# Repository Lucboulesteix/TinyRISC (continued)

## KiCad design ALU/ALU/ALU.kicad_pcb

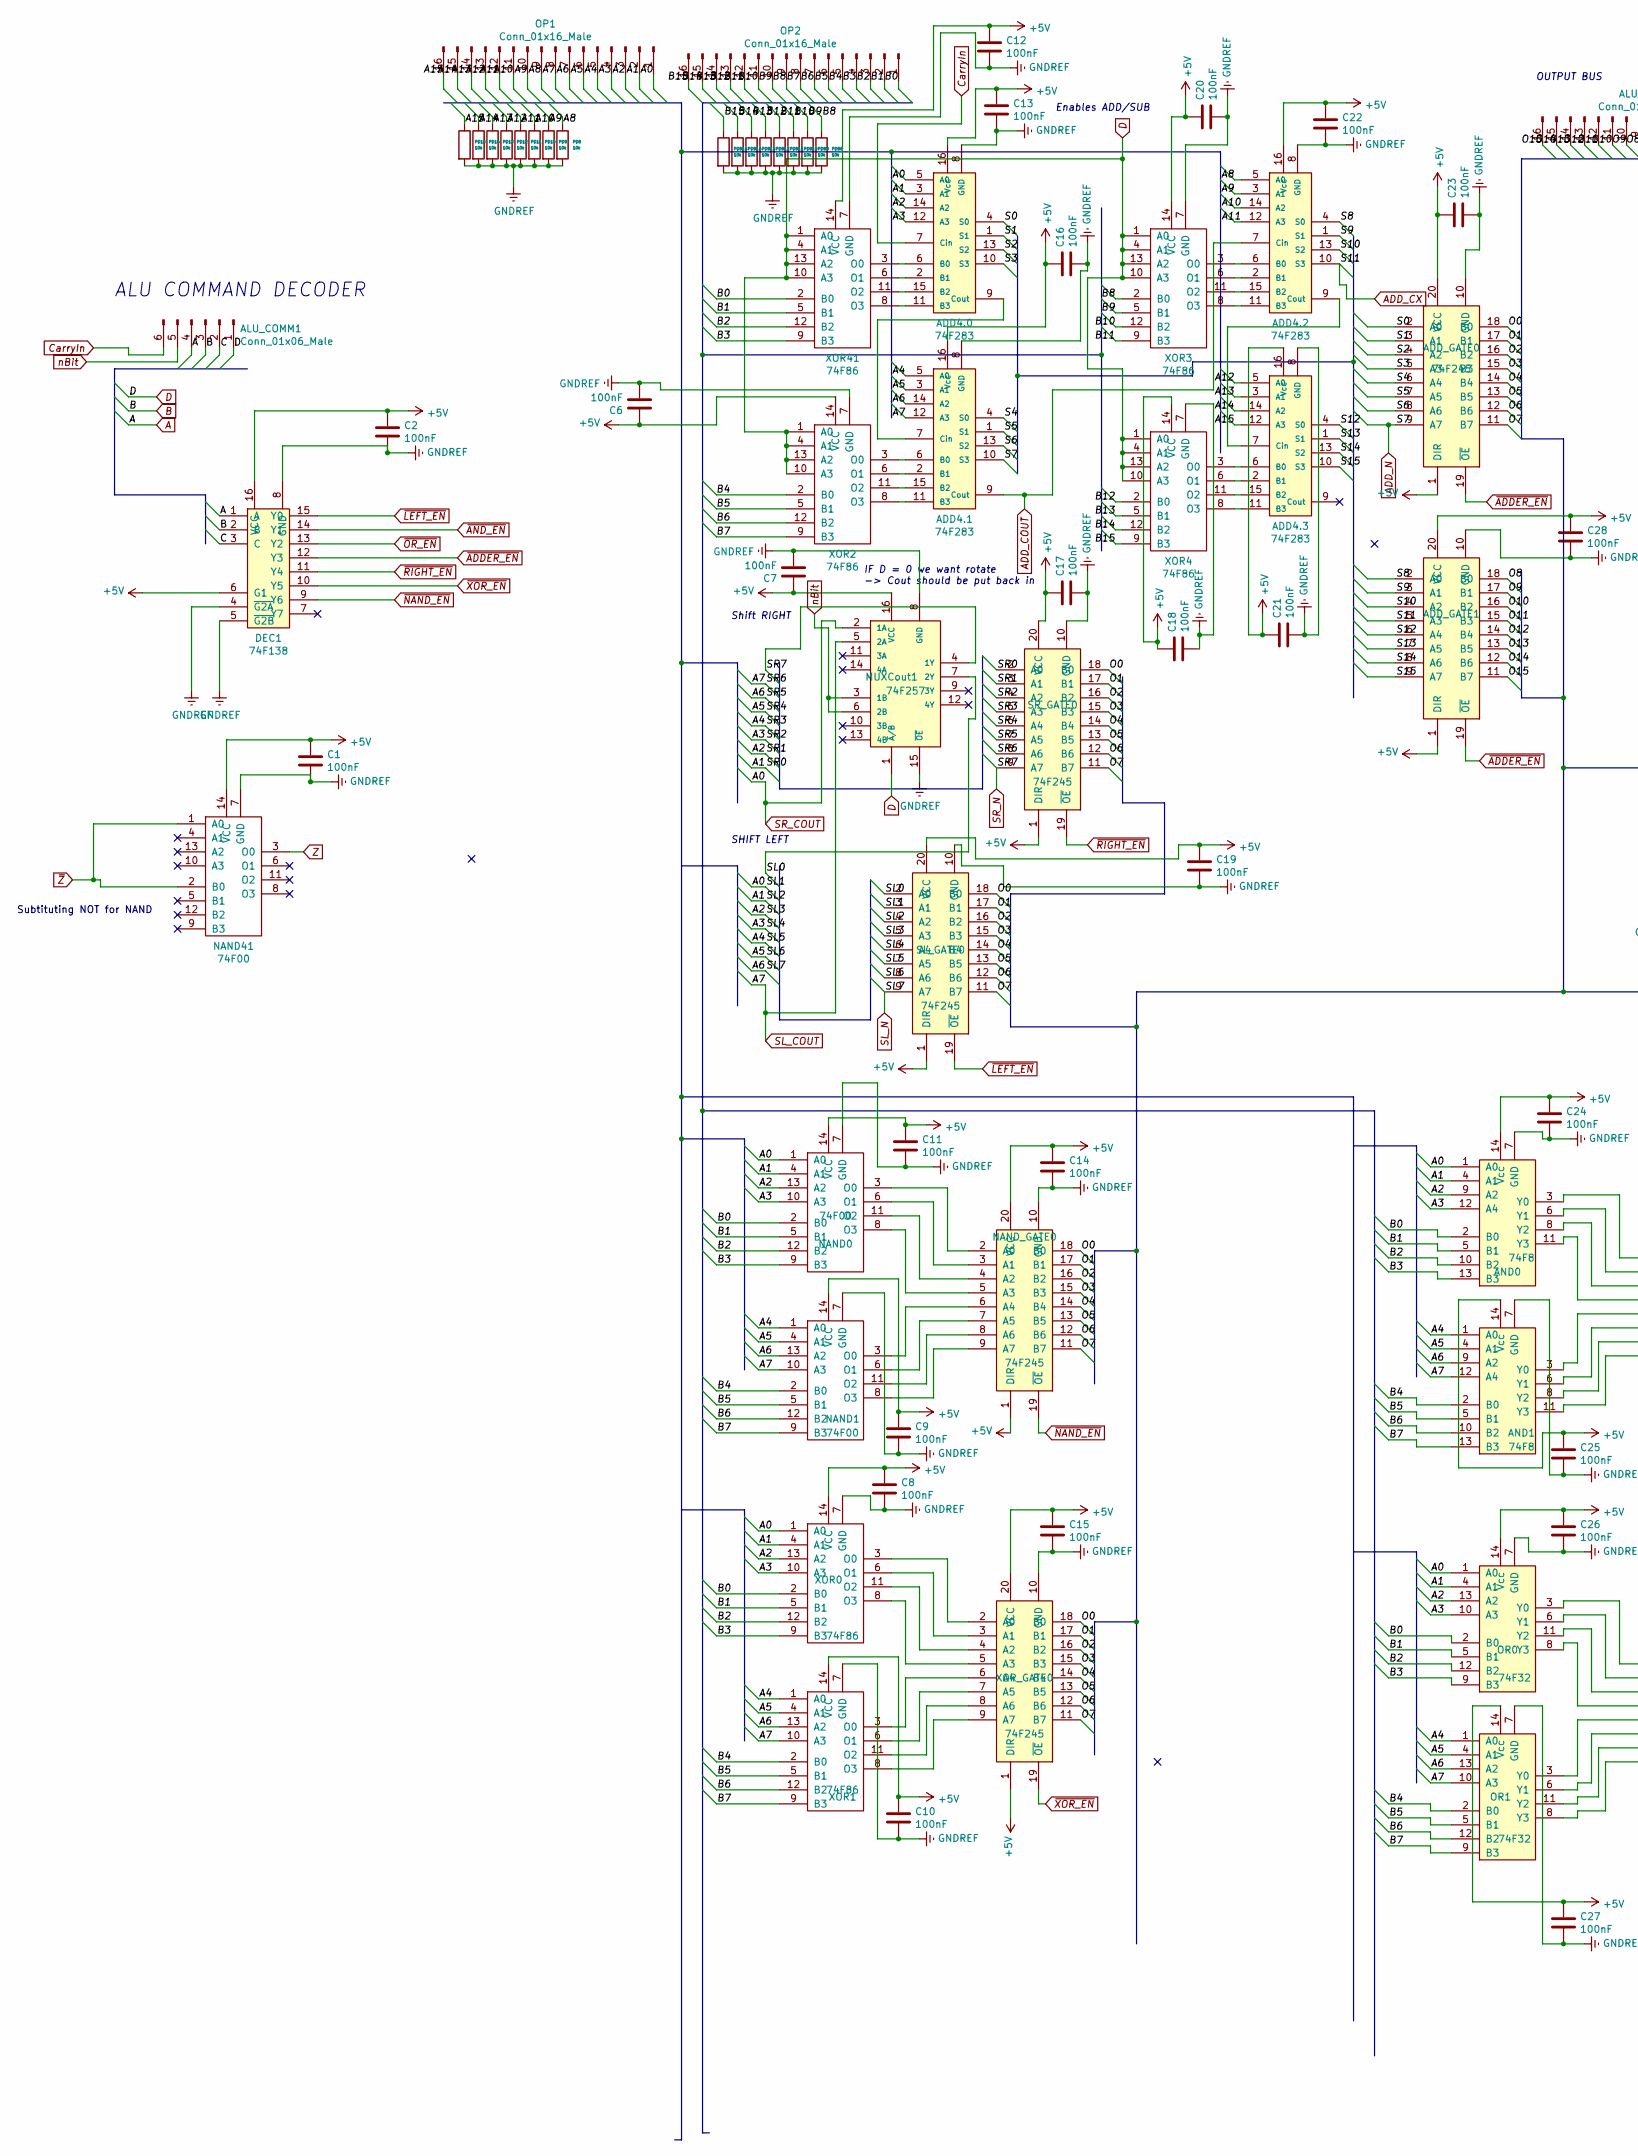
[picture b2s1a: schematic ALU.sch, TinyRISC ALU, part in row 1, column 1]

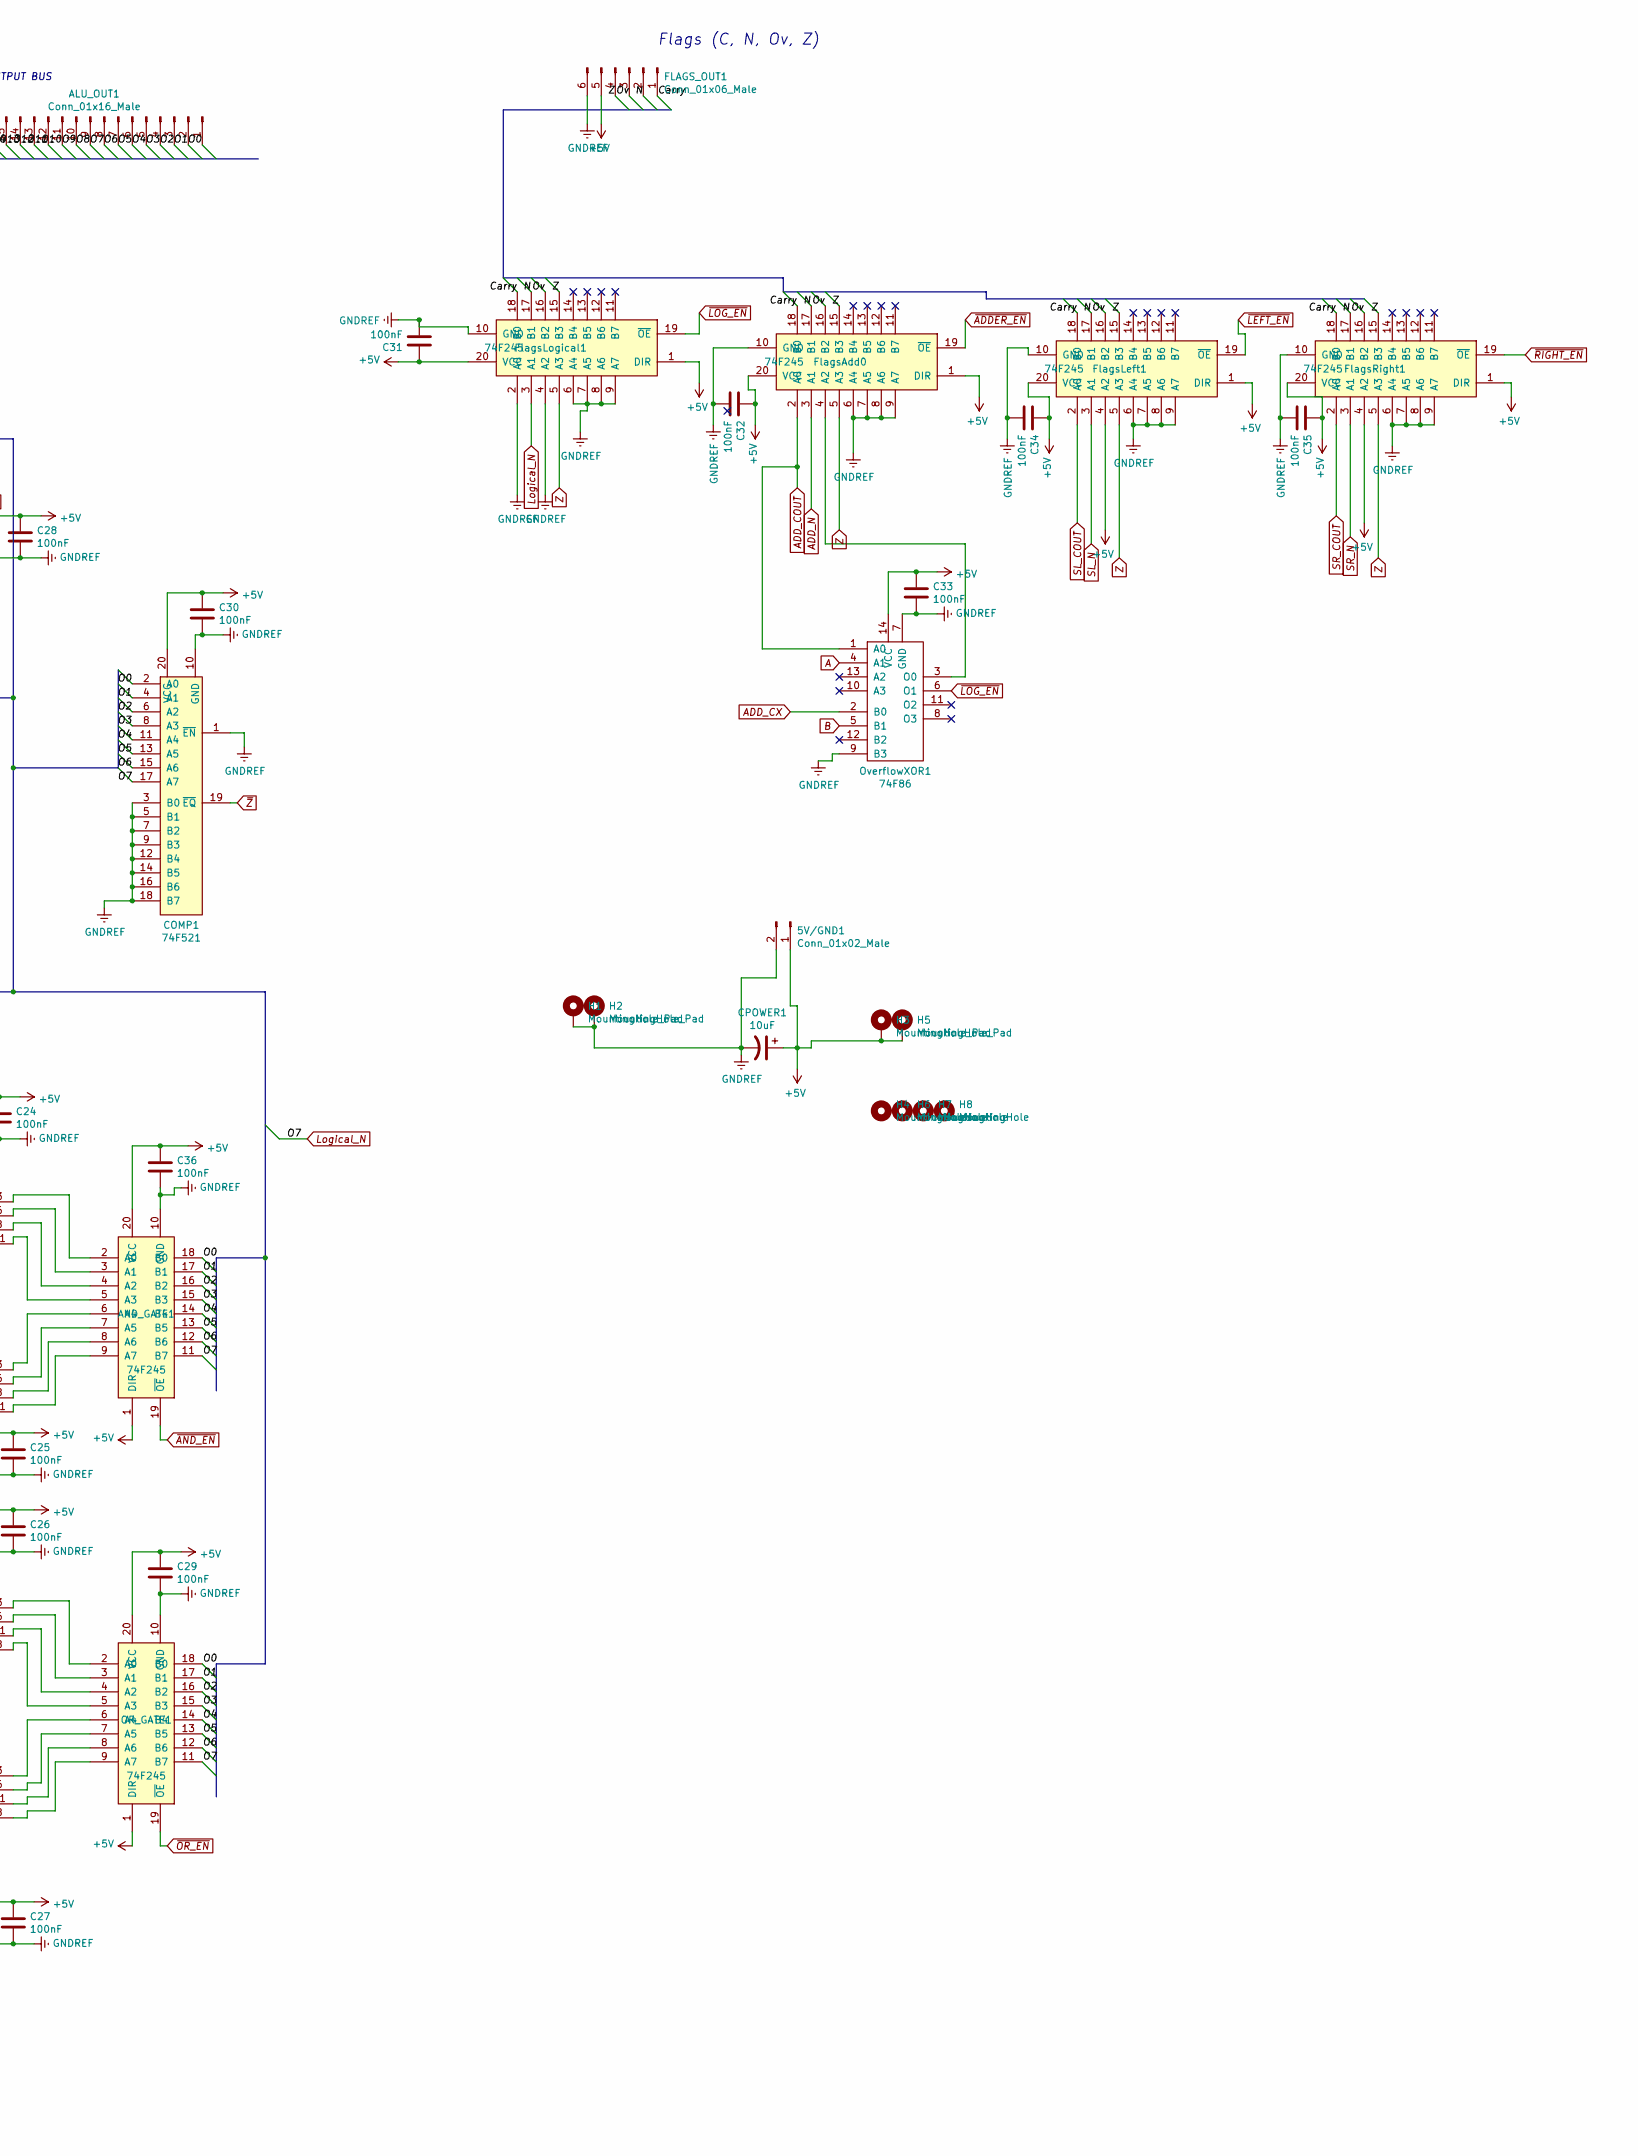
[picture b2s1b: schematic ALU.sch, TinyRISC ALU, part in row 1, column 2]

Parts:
5V/GND1: Conn_01x02_Male; JST_XH_B2B-XH-AM_1x02_P2.50mm_Vertical
ADD4.0, ADD4.1, ADD4.2, ADD4.3: 74F283; DIP-16_W7.62mm
ADD_GATE0, ADD_GATE1: 74F245; DIP-20_W7.62mm
ALU_COMM1: Conn_01x06_Male; 6pinIDC
ALU_OUT1: Conn_01x16_Male; 16pinIDC
AND0, AND1: 74F8; DIP-14_W7.62mm
AND_GATE1: 74F245; DIP-20_W7.62mm
C1, C2, C6, C7, C8, C9, C10, C11, C12, C13, C14, C15, C16, C17, C18, C19, C20, C21, C22, C23, C24, C25, C26, C27, C28, C29, C30, C31, C32, C33, C34, C35, C36: 100nF; C_Axial_L5.1mm_D3.1mm_P7.50mm_Horizontal
COMP1: 74F521; DIP-20_W7.62mm
CPOWER1: 10uF; CP_Radial_D8.0mm_P2.50mm
DEC1: 74F138; DIP-16_W7.62mm
FLAGS_OUT1: Conn_01x06_Male; 6pinIDC
FlagsAdd0: 74F245; DIP-20_W7.62mm
FlagsLeft1: 74F245; DIP-20_W7.62mm
FlagsLogical1: 74F245; DIP-20_W7.62mm
FlagsRight1: 74F245; DIP-20_W7.62mm
H1, H2, H3, H5: MountingHole_Pad; MountingHole_3.5mm_Pad_Via
H4, H6, H7, H8: MountingHole; MountingHole_3.5mm_Pad_Via
MUXCout1: 74F257; DIP-16_W7.62mm
NAND0, NAND1, NAND41: 74F00; DIP-14_W7.62mm
NAND_GATE0: 74F245; DIP-20_W7.62mm
OP1, OP2: Conn_01x16_Male; 16pinIDC
OR0, OR1: 74F32; DIP-14_W7.62mm
OR_GATE1: 74F245; DIP-20_W7.62mm
OverflowXOR1: 74F86; DIP-14_W7.62mm
PD8, PD9, PD10, PD11, PD12, PD13, PD14, PD15: 10k; R_Axial_DIN0204_L3.6mm_D1.6mm_P7.62mm_Horizontal
PDB8, PDB9, PDB10, PDB11, PDB12, PDB13, PDB14, PDB15: 10k; R_Axial_DIN0204_L3.6mm_D1.6mm_P7.62mm_Horizontal
SL_GATE0: 74F245; DIP-20_W7.62mm
SR_GATE0: 74F245; DIP-20_W7.62mm
XOR0, XOR1, XOR2, XOR3, XOR4, XOR41: 74F86; DIP-14_W7.62mm
XOR_GATE0: 74F245; DIP-20_W7.62mm

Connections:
+5V: 5V/GND1.1, ADD4.0.16 (Vcc), ADD4.1.16 (Vcc), ADD4.2.16 (Vcc), ADD4.3.16 (Vcc), ADD_GATE0.1 (DIR), ADD_GATE0.20 (VCC), ADD_GATE1.1 (DIR), ADD_GATE1.20 (VCC), AND0.14 (Vcc), AND1.14 (Vcc), AND_GATE1.1 (DIR), AND_GATE1.20 (VCC), C1.1, C2.1, C6.1, C7.1, C8.1, C9.1, C10.1, C11.1, C12.1, C13.1, C14.1, C15.1, C16.1, C17.1, C18.1, C19.1, C20.1, C21.1, C22.1, C23.1, C24.1, C25.1, C26.1, C27.1, C28.1, C29.1, C30.1, C31.1, C32.1, C33.1, C34.1, C35.1, C36.1, COMP1.20 (VCC), CPOWER1.1, DEC1.6 (G1), DEC1.16 (VCC), FLAGS_OUT1.5, FlagsAdd0.1 (DIR), FlagsAdd0.20 (VCC), FlagsLeft1.1 (DIR), FlagsLeft1.4 (A2), FlagsLeft1.20 (VCC), FlagsLogical1.1 (DIR), FlagsLogical1.20 (VCC), FlagsRight1.1 (DIR), FlagsRight1.4 (A2), FlagsRight1.20 (VCC), H3.1, H5.1, MUXCout1.16 (VCC), NAND0.14 (VCC), NAND1.14 (VCC), NAND41.14 (VCC), NAND_GATE0.1 (DIR), NAND_GATE0.20 (VCC), OR0.14 (Vcc), OR1.14 (Vcc), OR_GATE1.1 (DIR), OR_GATE1.20 (VCC), OverflowXOR1.14 (VCC), SL_GATE0.1 (DIR), SL_GATE0.20 (VCC), SR_GATE0.1 (DIR), SR_GATE0.20 (VCC), XOR0.14 (VCC), XOR1.14 (VCC), XOR2.14 (VCC), XOR3.14 (VCC), XOR4.14 (VCC), XOR41.14 (VCC), XOR_GATE0.1 (DIR), XOR_GATE0.20 (VCC)
/A1: ADD4.0.3 (A1), AND0.4 (A1), NAND0.4 (A1), OP1.2, OR0.4 (A1), SL_GATE0.4 (A2), SR_GATE0.2 (A0), XOR0.4 (A1)
/A2: ADD4.0.14 (A2), AND0.9 (A2), NAND0.13 (A2), OP1.3, OR0.13 (A2), SL_GATE0.5 (A3), SR_GATE0.3 (A1), XOR0.13 (A2)
/A3: ADD4.0.12 (A3), AND0.12 (A4), NAND0.10 (A3), OP1.4, OR0.10 (A3), SL_GATE0.6 (A4), SR_GATE0.4 (A2), XOR0.10 (A3)
/A4: ADD4.1.5 (A0), AND1.1 (A0), NAND1.1 (A0), OP1.5, OR1.1 (A0), SL_GATE0.7 (A5), SR_GATE0.5 (A3), XOR1.1 (A0)
/A5: ADD4.1.3 (A1), AND1.4 (A1), NAND1.4 (A1), OP1.6, OR1.4 (A1), SL_GATE0.8 (A6), SR_GATE0.6 (A4), XOR1.4 (A1)
/A8: ADD4.2.5 (A0), OP1.9, PD8.1
/A9: ADD4.2.3 (A1), OP1.10, PD9.1
/A10: ADD4.2.14 (A2), OP1.11, PD10.1
/A11: ADD4.2.12 (A3), OP1.12, PD11.1
/A12: ADD4.3.5 (A0), OP1.13, PD12.1
/A13: ADD4.3.3 (A1), OP1.14, PD13.1
/A14: ADD4.3.14 (A2), OP1.15, PD14.1
/A15: ADD4.3.12 (A3), OP1.16, PD15.1
/B0: AND0.2 (B0), NAND0.2 (B0), OP2.1, OR0.2 (B0), XOR0.2 (B0), XOR41.2 (B0)
/B1: AND0.5 (B1), NAND0.5 (B1), OP2.2, OR0.5 (B1), XOR0.5 (B1), XOR41.5 (B1)
/B2: AND0.10 (B2), NAND0.12 (B2), OP2.3, OR0.12 (B2), XOR0.12 (B2), XOR41.12 (B2)
/B3: AND0.13 (B3), NAND0.9 (B3), OP2.4, OR0.9 (B3), XOR0.9 (B3), XOR41.9 (B3)
/B4: AND1.2 (B0), NAND1.2 (B0), OP2.5, OR1.2 (B0), XOR1.2 (B0), XOR2.2 (B0)
/B5: AND1.5 (B1), NAND1.5 (B1), OP2.6, OR1.5 (B1), XOR1.5 (B1), XOR2.5 (B1)
/B6: AND1.10 (B2), NAND1.12 (B2), OP2.7, OR1.12 (B2), XOR1.12 (B2), XOR2.12 (B2)
/B7: AND1.13 (B3), NAND1.9 (B3), OP2.8, OR1.9 (B3), XOR1.9 (B3), XOR2.9 (B3)
/B8: OP2.9, PDB8.1, XOR3.2 (B0)
/B9: OP2.10, PDB9.1, XOR3.5 (B1)
/B10: OP2.11, PDB10.1, XOR3.12 (B2)
/B11: OP2.12, PDB11.1, XOR3.9 (B3)
/B12: OP2.13, PDB12.1, XOR4.2 (B0)
/B13: OP2.14, PDB13.1, XOR4.5 (B1)
/B14: OP2.15, PDB14.1, XOR4.12 (B2)
/B15: OP2.16, PDB15.1, XOR4.9 (B3)
/C: ALU_COMM1.2, DEC1.3 (C)
/Carry: FLAGS_OUT1.1, FlagsAdd0.18 (B0), FlagsLeft1.18 (B0), FlagsLogical1.18 (B0), FlagsRight1.18 (B0)
/N: FLAGS_OUT1.2, FlagsAdd0.17 (B1), FlagsLeft1.17 (B1), FlagsLogical1.17 (B1), FlagsRight1.17 (B1)
/O0: ADD_GATE0.18 (B0), ALU_OUT1.1, AND_GATE1.18 (B0), COMP1.2 (A0), NAND_GATE0.18 (B0), OR_GATE1.18 (B0), SL_GATE0.18 (B0), SR_GATE0.18 (B0), XOR_GATE0.18 (B0)
/O1: ADD_GATE0.17 (B1), ALU_OUT1.2, AND_GATE1.17 (B1), COMP1.4 (A1), NAND_GATE0.17 (B1), OR_GATE1.17 (B1), SL_GATE0.17 (B1), SR_GATE0.17 (B1), XOR_GATE0.17 (B1)
/O2: ADD_GATE0.16 (B2), ALU_OUT1.3, AND_GATE1.16 (B2), COMP1.6 (A2), NAND_GATE0.16 (B2), OR_GATE1.16 (B2), SL_GATE0.16 (B2), SR_GATE0.16 (B2), XOR_GATE0.16 (B2)
/O3: ADD_GATE0.15 (B3), ALU_OUT1.4, AND_GATE1.15 (B3), COMP1.8 (A3), NAND_GATE0.15 (B3), OR_GATE1.15 (B3), SL_GATE0.15 (B3), SR_GATE0.15 (B3), XOR_GATE0.15 (B3)
/O4: ADD_GATE0.14 (B4), ALU_OUT1.5, AND_GATE1.14 (B4), COMP1.11 (A4), NAND_GATE0.14 (B4), OR_GATE1.14 (B4), SL_GATE0.14 (B4), SR_GATE0.14 (B4), XOR_GATE0.14 (B4)
/O5: ADD_GATE0.13 (B5), ALU_OUT1.6, AND_GATE1.13 (B5), COMP1.13 (A5), NAND_GATE0.13 (B5), OR_GATE1.13 (B5), SL_GATE0.13 (B5), SR_GATE0.13 (B5), XOR_GATE0.13 (B5)
/O6: ADD_GATE0.12 (B6), ALU_OUT1.7, AND_GATE1.12 (B6), COMP1.15 (A6), NAND_GATE0.12 (B6), OR_GATE1.12 (B6), SL_GATE0.12 (B6), SR_GATE0.12 (B6), XOR_GATE0.12 (B6)
/O8: ADD_GATE1.18 (B0), ALU_OUT1.9
/O9: ADD_GATE1.17 (B1), ALU_OUT1.10
/O10: ADD_GATE1.16 (B2), ALU_OUT1.11
/O11: ADD_GATE1.15 (B3), ALU_OUT1.12
/O12: ADD_GATE1.14 (B4), ALU_OUT1.13
/O13: ADD_GATE1.13 (B5), ALU_OUT1.14
/O14: ADD_GATE1.12 (B6), ALU_OUT1.15
/O15: ADD_GATE1.11 (B7), ALU_OUT1.16
/Ov: FLAGS_OUT1.3, FlagsAdd0.16 (B2), FlagsLeft1.16 (B2), FlagsLogical1.16 (B2), FlagsRight1.16 (B2)
/S0: ADD4.0.4 (S0), ADD_GATE0.2 (A0)
/S1: ADD4.0.1 (S1), ADD_GATE0.3 (A1)
/S2: ADD4.0.13 (S2), ADD_GATE0.4 (A2)
/S3: ADD4.0.10 (S3), ADD_GATE0.5 (A3)
/S4: ADD4.1.4 (S0), ADD_GATE0.6 (A4)
/S5: ADD4.1.1 (S1), ADD_GATE0.7 (A5)
/S6: ADD4.1.13 (S2), ADD_GATE0.8 (A6)
/S8: ADD4.2.4 (S0), ADD_GATE1.2 (A0)
/S9: ADD4.2.1 (S1), ADD_GATE1.3 (A1)
/S10: ADD4.2.13 (S2), ADD_GATE1.4 (A2)
/S12: ADD4.3.4 (S0), ADD_GATE1.6 (A4)
/S13: ADD4.3.1 (S1), ADD_GATE1.7 (A5)
/S14: ADD4.3.13 (S2), ADD_GATE1.8 (A6)
/S15: ADD4.3.10 (S3), ADD_GATE1.9 (A7)
/SL0: MUXCout1.7 (2Y), SL_GATE0.2 (A0)
A: ALU_COMM1.4, DEC1.1 (A), OverflowXOR1.4 (A1)
ADD_COUT: ADD4.1.9 (Cout), ADD4.2.7 (Cin), FlagsAdd0.2 (A0), OverflowXOR1.1 (A0)
ADD_CX: ADD4.2.10 (S3), ADD_GATE1.5 (A3), OverflowXOR1.2 (B0)
ADD_N: ADD4.1.10 (S3), ADD_GATE0.9 (A7), FlagsAdd0.3 (A1)
B: ALU_COMM1.3, DEC1.2 (B), OverflowXOR1.5 (B1)
CarryIn: ADD4.0.7 (Cin), ALU_COMM1.6
D: ALU_COMM1.1, MUXCout1.1 (~A~/B), XOR2.1 (A0), XOR2.4 (A1), XOR2.10 (A3), XOR2.13 (A2), XOR3.1 (A0), XOR3.4 (A1), XOR3.10 (A3), XOR3.13 (A2), XOR4.1 (A0), XOR4.4 (A1), XOR4.10 (A3), XOR4.13 (A2), XOR41.1 (A0), XOR41.4 (A1), XOR41.10 (A3), XOR41.13 (A2)
GNDREF: 5V/GND1.2, ADD4.0.8 (GND), ADD4.1.8 (GND), ADD4.2.8 (GND), ADD4.3.8 (GND), ADD_GATE0.10 (GND), ADD_GATE1.10 (GND), AND0.7 (GND), AND1.7 (GND), AND_GATE1.10 (GND), C1.2, C2.2, C6.2, C7.2, C8.2, C9.2, C10.2, C11.2, C12.2, C13.2, C14.2, C15.2, C16.2, C17.2, C18.2, C19.2, C20.2, C21.2, C22.2, C23.2, C24.2, C25.2, C26.2, C27.2, C28.2, C29.2, C30.2, C31.2, C32.2, C33.2, C34.2, C35.2, C36.2, COMP1.1 (~EN), COMP1.3 (B0), COMP1.5 (B1), COMP1.7 (B2), COMP1.9 (B3), COMP1.10 (GND), COMP1.12 (B4), COMP1.14 (B5), COMP1.16 (B6), COMP1.18 (B7), CPOWER1.2, DEC1.4 (~G2A), DEC1.5 (~G2B), DEC1.8 (GND), FLAGS_OUT1.6, FlagsAdd0.6 (A4), FlagsAdd0.7 (A5), FlagsAdd0.8 (A6), FlagsAdd0.9 (A7), FlagsAdd0.10 (GND), FlagsLeft1.6 (A4), FlagsLeft1.7 (A5), FlagsLeft1.8 (A6), FlagsLeft1.9 (A7), FlagsLeft1.10 (GND), FlagsLogical1.2 (A0), FlagsLogical1.4 (A2), FlagsLogical1.6 (A4), FlagsLogical1.7 (A5), FlagsLogical1.8 (A6), FlagsLogical1.9 (A7), FlagsLogical1.10 (GND), FlagsRight1.6 (A4), FlagsRight1.7 (A5), FlagsRight1.8 (A6), FlagsRight1.9 (A7), FlagsRight1.10 (GND), H1.1, H2.1, MUXCout1.8 (GND), MUXCout1.15 (~OE), NAND0.7 (GND), NAND1.7 (GND), NAND41.7 (GND), NAND_GATE0.10 (GND), OR0.7 (GND), OR1.7 (GND), OR_GATE1.10 (GND), OverflowXOR1.7 (GND), OverflowXOR1.9 (B3), PD8.2, PD9.2, PD10.2, PD11.2, PD12.2, PD13.2, PD14.2, PD15.2, PDB8.2, PDB9.2, PDB10.2, PDB11.2, PDB12.2, PDB13.2, PDB14.2, PDB15.2, SL_GATE0.10 (GND), SR_GATE0.10 (GND), XOR0.7 (GND), XOR1.7 (GND), XOR2.7 (GND), XOR3.7 (GND), XOR4.7 (GND), XOR41.7 (GND), XOR_GATE0.10 (GND)
Logical_N: ADD_GATE0.11 (B7), ALU_OUT1.8, AND_GATE1.11 (B7), COMP1.17 (A7), FlagsLogical1.3 (A1), NAND_GATE0.11 (B7), OR_GATE1.11 (B7), SL_GATE0.11 (B7), SR_GATE0.11 (B7), XOR_GATE0.11 (B7)
unnamed: ADD4.0.2 (B1), XOR41.6 (O1)
unnamed: ADD4.0.6 (B0), XOR41.3 (O0)
unnamed: ADD4.0.9 (Cout), ADD4.1.7 (Cin)
unnamed: ADD4.0.11 (B3), XOR41.8 (O3)
unnamed: ADD4.0.15 (B2), XOR41.11 (O2)
unnamed: ADD4.1.2 (B1), XOR2.6 (O1)
unnamed: ADD4.1.6 (B0), XOR2.3 (O0)
unnamed: ADD4.1.11 (B3), XOR2.8 (O3)
unnamed: ADD4.1.15 (B2), XOR2.11 (O2)
unnamed: ADD4.2.2 (B1), XOR3.6 (O1)
unnamed: ADD4.2.6 (B0), XOR3.3 (O0)
unnamed: ADD4.2.9 (Cout), ADD4.3.7 (Cin)
unnamed: ADD4.2.11 (B3), XOR3.8 (O3)
unnamed: ADD4.2.15 (B2), XOR3.11 (O2)
unnamed: ADD4.3.2 (B1), XOR4.6 (O1)
unnamed: ADD4.3.6 (B0), XOR4.3 (O0)
unnamed: ADD4.3.11 (B3), XOR4.8 (O3)
unnamed: ADD4.3.15 (B2), XOR4.11 (O2)
unnamed: AND0.3 (Y0), AND_GATE1.2 (A0)
unnamed: AND0.6 (Y1), AND_GATE1.3 (A1)
unnamed: AND0.8 (Y2), AND_GATE1.4 (A2)
unnamed: AND0.11 (Y3), AND_GATE1.5 (A3)
unnamed: AND1.3 (Y0), AND_GATE1.6 (A4)
unnamed: AND1.6 (Y1), AND_GATE1.7 (A5)
unnamed: AND1.8 (Y2), AND_GATE1.8 (A6)
unnamed: AND1.11 (Y3), AND_GATE1.9 (A7)
unnamed: FlagsAdd0.4 (A2), OverflowXOR1.3 (O0)
unnamed: NAND0.3 (O0), NAND_GATE0.2 (A0)
unnamed: NAND0.6 (O1), NAND_GATE0.3 (A1)
unnamed: NAND0.8 (O3), NAND_GATE0.5 (A3)
unnamed: NAND0.11 (O2), NAND_GATE0.4 (A2)
unnamed: NAND1.3 (O0), NAND_GATE0.6 (A4)
unnamed: NAND1.6 (O1), NAND_GATE0.7 (A5)
unnamed: NAND1.8 (O3), NAND_GATE0.9 (A7)
unnamed: NAND1.11 (O2), NAND_GATE0.8 (A6)
unnamed: OR0.3 (Y0), OR_GATE1.2 (A0)
unnamed: OR0.6 (Y1), OR_GATE1.3 (A1)
unnamed: OR0.8 (Y3), OR_GATE1.5 (A3)
unnamed: OR0.11 (Y2), OR_GATE1.4 (A2)
unnamed: OR1.3 (Y0), OR_GATE1.6 (A4)
unnamed: OR1.6 (Y1), OR_GATE1.7 (A5)
unnamed: OR1.8 (Y3), OR_GATE1.9 (A7)
unnamed: OR1.11 (Y2), OR_GATE1.8 (A6)
unnamed: XOR0.3 (O0), XOR_GATE0.2 (A0)
unnamed: XOR0.6 (O1), XOR_GATE0.3 (A1)
unnamed: XOR0.8 (O3), XOR_GATE0.5 (A3)
unnamed: XOR0.11 (O2), XOR_GATE0.4 (A2)
unnamed: XOR1.3 (O0), XOR_GATE0.6 (A4)
unnamed: XOR1.6 (O1), XOR_GATE0.7 (A5)
unnamed: XOR1.8 (O3), XOR_GATE0.9 (A7)
unnamed: XOR1.11 (O2), XOR_GATE0.8 (A6)
SL_COUT: ADD4.1.12 (A3), AND1.12 (A4), FlagsLeft1.2 (A0), MUXCout1.5 (2A), NAND1.10 (A3), OP1.8, OR1.10 (A3), SR_GATE0.8 (A6), XOR1.10 (A3)
SL_N: ADD4.1.14 (A2), AND1.9 (A2), FlagsLeft1.3 (A1), NAND1.13 (A2), OP1.7, OR1.13 (A2), SL_GATE0.9 (A7), SR_GATE0.7 (A5), XOR1.13 (A2)
SR_COUT: ADD4.0.5 (A0), AND0.1 (A0), FlagsRight1.2 (A0), MUXCout1.2 (1A), NAND0.1 (A0), OP1.1, OR0.1 (A0), SL_GATE0.3 (A1), XOR0.1 (A0)
SR_N: FlagsRight1.3 (A1), MUXCout1.4 (1Y), SR_GATE0.9 (A7)
Z: FLAGS_OUT1.4, FlagsAdd0.5 (A3), FlagsAdd0.15 (B3), FlagsLeft1.5 (A3), FlagsLeft1.15 (B3), FlagsLogical1.5 (A3), FlagsLogical1.15 (B3), FlagsRight1.5 (A3), FlagsRight1.15 (B3), NAND41.3 (O0)
nBit: ALU_COMM1.5, MUXCout1.3 (1B), MUXCout1.6 (2B)
~ADDER_EN: ADD_GATE0.19 (~OE), ADD_GATE1.19 (~OE), DEC1.12 (Y3), FlagsAdd0.19 (~OE)
~AND_EN: AND_GATE1.19 (~OE), DEC1.14 (Y1)
~LEFT_EN: DEC1.15 (Y0), FlagsLeft1.19 (~OE), SL_GATE0.19 (~OE)
~LOG_EN: FlagsLogical1.19 (~OE), OverflowXOR1.6 (O1)
~NAND_EN: DEC1.9 (Y6), NAND_GATE0.19 (~OE)
~OR_EN: DEC1.13 (Y2), OR_GATE1.19 (~OE)
~RIGHT_EN: DEC1.11 (Y4), FlagsRight1.19 (~OE), SR_GATE0.19 (~OE)
~XOR_EN: DEC1.10 (Y5), XOR_GATE0.19 (~OE)
~Z: COMP1.19 (~EQ), NAND41.1 (A0), NAND41.2 (B0)

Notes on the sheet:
ALU COMMAND DECODER
Enables ADD/SUB
Shift RIGHT
IF D = 0 we want rotate -> Cout should be put back in
SHIFT LEFT
OUTPUT BUS
Flags (C, N, Ov, Z)
Subtituting NOT for NAND

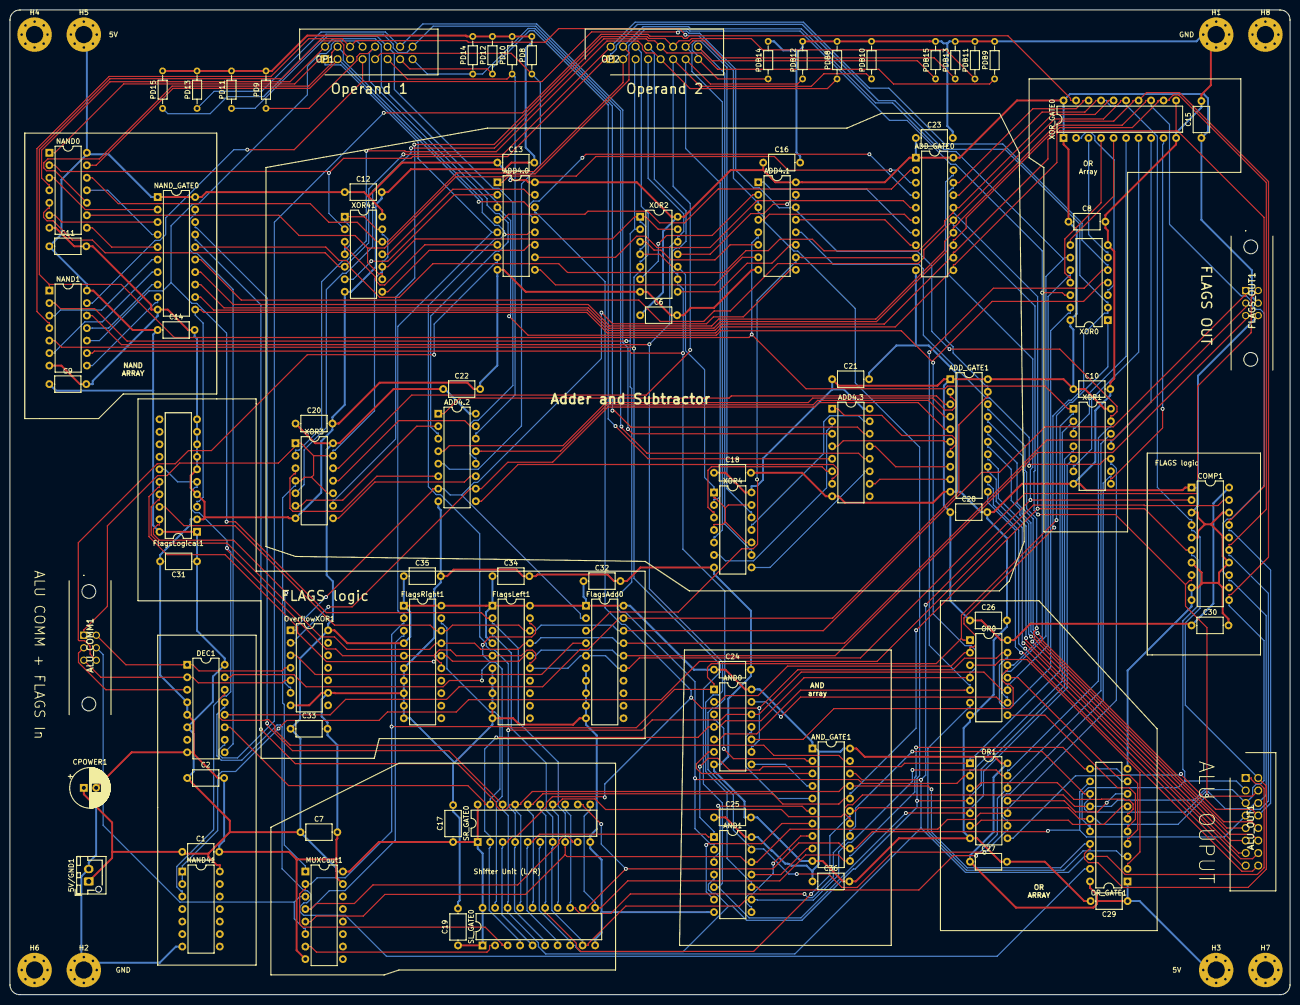
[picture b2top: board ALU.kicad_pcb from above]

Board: 2 copper layers, 260.0 x 200.0 mm, 97 parts (0 on the bottom side), 139 nets.

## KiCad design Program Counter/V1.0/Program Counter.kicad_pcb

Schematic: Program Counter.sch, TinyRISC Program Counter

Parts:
ADD4.1, ADD4.2, ADD4.3, ADD4.4: 74F283; DIP-16_W7.62mm
C1, C2, C4, C5, C6, C7, C8, C9, C11, C12, C13: 100nF; C_Axial_L5.1mm_D3.1mm_P7.50mm_Horizontal
C3: C?; C_Axial_L5.1mm_D3.1mm_P7.50mm_Horizontal
C10: 100nf; C_Axial_L5.1mm_D3.1mm_P7.50mm_Horizontal
C_BOARD1: 10uF; CP_Radial_D8.0mm_P2.50mm
H1, H2, H3, H4: MountingHole; MountingHole_3.5mm_Pad_Via
H5, H6, H7, H8: MountingHole_Pad; MountingHole_3.5mm_Pad_Via
J1: PC_OUT; 16pinIDC
J2: PC_OFFS; 16pinIDC
J3: Control; JST_XH_B04B-XH-A_04x2.50mm_Straight
J4: Clock; 1pin
J5: POWER/GND; JST_NV_B02P-NV_2x5.00mm_Vertical
MUXA1, MUXA2, MUXA3, MUXA4: 74F257; DIP-16_W7.62mm
MUXB1, MUXB2: 74F257; DIP-16_W7.62mm
POT1: 1K; Potentiometer_Trimmer_ACP_CA14h5_Vertical_Px5.0mm_Py10.0mm
R4, R5, R10, R14: 10K; R_Axial_DIN0204_L3.6mm_D1.6mm_P7.62mm_Horizontal
R6: 100; R_Axial_DIN0204_L3.6mm_D1.6mm_P7.62mm_Horizontal
REG8.1, REG8.2: 74F825; DIP-24_W7.62mm

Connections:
+5V: ADD4.1.16, ADD4.2.16, ADD4.3.16, ADD4.4.16, C1.2, C2.2, C4.1, C5.1, C6.1, C7.1, C8.2, C9.2, C10.2, C11.2, C12.2, C13.2, C_BOARD1.1, H5.1, H6.1, J5.2, MUXA1.16, MUXA2.16, MUXA3.16, MUXA4.16, MUXB1.5, MUXB1.16, MUXB2.16, R6.1, REG8.1.24, REG8.2.24
/N0: MUXA1.4, REG8.1.3
/N1: MUXA1.7, REG8.1.4
/N2: MUXA1.9, REG8.1.5
/N3: MUXA1.12, REG8.1.6
/N4: MUXA2.4, REG8.1.7
/N5: MUXA2.7, REG8.1.8
/N6: MUXA2.9, REG8.1.9
/N7: MUXA2.12, REG8.1.10
/N8: MUXA3.4, REG8.2.3
/N9: MUXA3.7, REG8.2.4
/N10: MUXA3.9, REG8.2.5
/N11: MUXA3.12, REG8.2.6
/N12: MUXA4.4, REG8.2.7
/N13: MUXA4.7, REG8.2.8
/N14: MUXA4.9, REG8.2.9
/N15: MUXA4.12, REG8.2.10
/O0: J1.1, REG8.1.22
/O1: J1.2, REG8.1.21
/O2: J1.3, REG8.1.20
/O3: J1.4, REG8.1.19
/O4: J1.5, REG8.1.18
/O5: J1.6, REG8.1.17
/O6: J1.7, REG8.1.16
/O7: J1.8, REG8.1.15
/O8: J1.9, REG8.2.22
/O9: J1.10, REG8.2.21
/O10: J1.11, REG8.2.20
/O11: J1.12, REG8.2.19
/O12: J1.13, REG8.2.18
/O13: J1.14, REG8.2.17
/O14: J1.15, REG8.2.16
/O15: J1.16, REG8.2.15
/OFF0: ADD4.1.6, J2.1, MUXA1.3, MUXB1.3
/OFF1: ADD4.1.2, J2.2, MUXA1.6, MUXB1.6
/OFF2: ADD4.1.15, J2.3, MUXA1.10, MUXB1.10
/OFF3: ADD4.1.11, J2.4, MUXA1.13, MUXB1.13
/OFF4: ADD4.2.6, J2.5, MUXA2.3, MUXB2.3
/OFF5: ADD4.2.2, J2.6, MUXA2.6, MUXB2.6
/OFF6: ADD4.2.15, J2.7, MUXA2.10, MUXB2.10
/OFF7: ADD4.2.11, J2.8, MUXA2.13, MUXB2.13
/OFF8: ADD4.3.6, J2.9, MUXA3.3
/OFF9: ADD4.3.2, J2.10, MUXA3.6
/OFF10: ADD4.3.15, J2.11, MUXA3.10
/OFF11: ADD4.3.11, J2.12, MUXA3.13
/OFF12: ADD4.4.6, J2.13, MUXA4.3
/OFF13: ADD4.4.2, J2.14, MUXA4.6
/OFF14: ADD4.4.15, J2.15, MUXA4.10
/OFF15: ADD4.4.11, J2.16, MUXA4.13
/R0: ADD4.1.5, MUXB1.4
/R1: ADD4.1.3, MUXB1.7
/R2: ADD4.1.14, MUXB1.9
/R3: ADD4.1.12, MUXB1.12
/R4: ADD4.2.5, MUXB2.4
/R5: ADD4.2.3, MUXB2.7
/R6: ADD4.2.14, MUXB2.9
/R7: ADD4.2.12, MUXB2.12
/S0: ADD4.1.4, MUXA1.2
/S1: ADD4.1.1, MUXA1.5
/S2: ADD4.1.13, MUXA1.11
/S3: ADD4.1.10, MUXA1.14
/S4: ADD4.2.4, MUXA2.2
/S5: ADD4.2.1, MUXA2.5
/S6: ADD4.2.13, MUXA2.11
/S7: ADD4.2.10, MUXA2.14
/S8: ADD4.3.4, MUXA3.2
/S9: ADD4.3.1, MUXA3.5
/S10: ADD4.3.13, MUXA3.11
/S11: ADD4.3.10, MUXA3.14
/S12: ADD4.4.4, MUXA4.2
/S13: ADD4.4.1, MUXA4.5
/S14: ADD4.4.13, MUXA4.11
/S15: ADD4.4.10, MUXA4.14
CLK: J4.1, REG8.1.13, REG8.2.13
GNDREF: ADD4.1.7, ADD4.1.8, ADD4.2.8, ADD4.3.8, ADD4.4.8, C1.1, C2.1, C3.2, C4.2, C5.2, C6.2, C7.2, C8.1, C9.1, C10.1, C11.1, C12.1, C13.1, C_BOARD1.2, H7.1, H8.1, J5.1, MUXA1.8, MUXA1.15, MUXA2.8, MUXA3.8, MUXA3.15, MUXA4.8, MUXA4.15, MUXB1.2, MUXB1.8, MUXB1.11, MUXB1.14, MUXB1.15, MUXB2.2, MUXB2.5, MUXB2.8, MUXB2.11, MUXB2.14, MUXB2.15, R4.1, R5.1, R10.1, R14.1, REG8.1.1, REG8.1.2, REG8.1.12, REG8.1.23, REG8.2.1, REG8.2.2, REG8.2.12, REG8.2.23
JMP_ABS: J3.4, MUXA1.1, MUXA2.1, MUXA3.1, MUXA4.1, R4.2; also elsewhere on the board
JMP_IN: J3.1, MUXB1.1, MUXB2.1, R14.2; also elsewhere on the board
unnamed: ADD4.1.9, ADD4.2.7
unnamed: ADD4.2.9, ADD4.3.7
unnamed: ADD4.3.9, ADD4.4.7
unnamed: ADD4.4.9, R10.2
unnamed: POT1.1, R6.2
REL_SIGN: ADD4.3.3, ADD4.3.5, ADD4.3.12, ADD4.3.14, ADD4.4.3, ADD4.4.5, ADD4.4.12, ADD4.4.14, J3.2; also elsewhere on the board
~PC_CLR: C3.1, POT1.2, REG8.1.11, REG8.2.11
~STALL: J3.3, R5.2, REG8.1.14, REG8.2.14; also elsewhere on the board

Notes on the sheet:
RC circuit to reset PC at poweron At startup, CLR is held low, clearing PC. After t = 0.5RC PC is no longer being cleared
lowest nibble
highest nibble
Increment +2

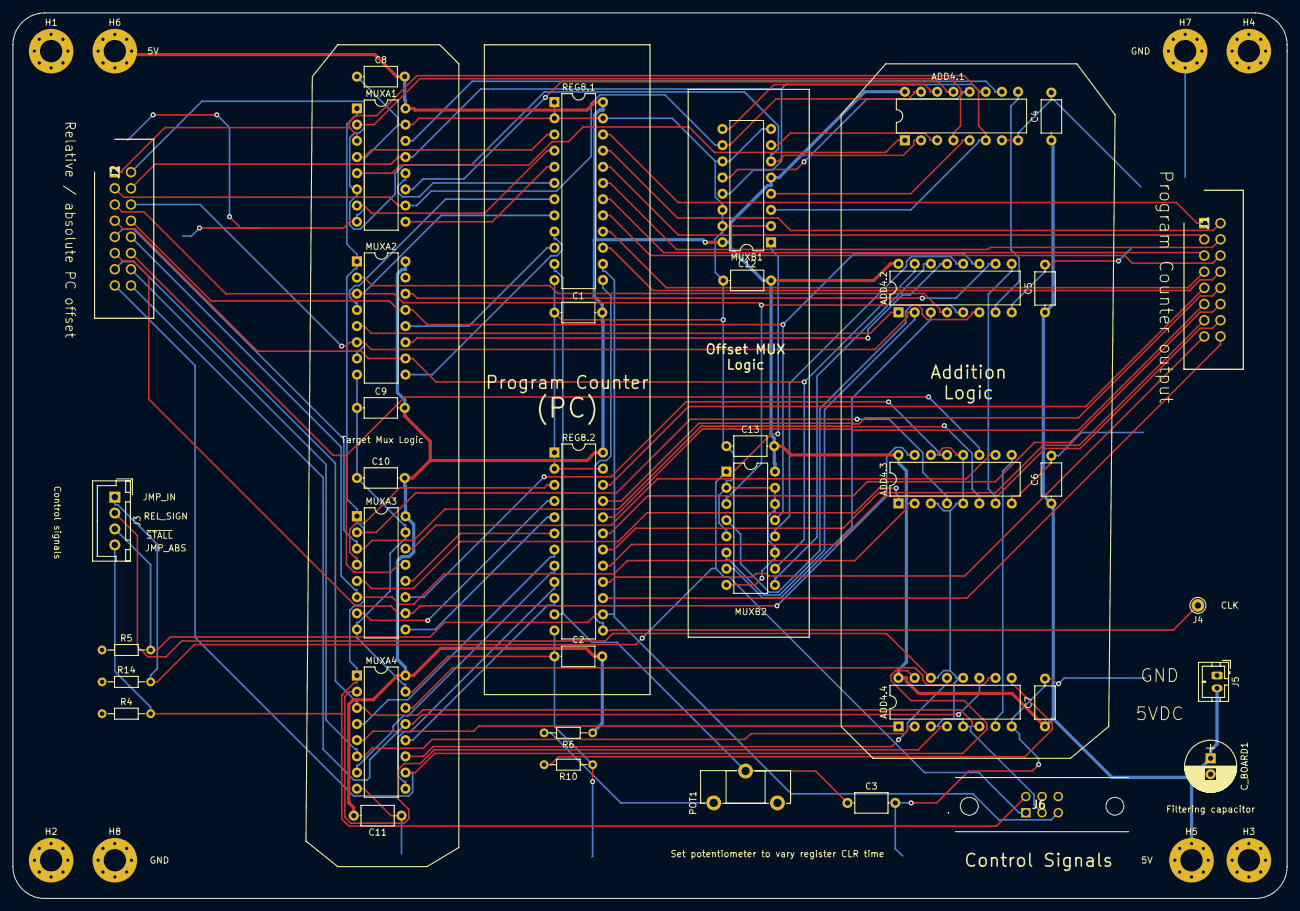
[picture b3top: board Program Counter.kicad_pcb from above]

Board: 2 copper layers, 200.0 x 139.0 mm, 46 parts (0 on the bottom side), 85 nets.

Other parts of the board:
J6: Control; 6pinIDC

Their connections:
JMP_ABS: J6.4; also elsewhere on the board
JMP_IN: J6.1; also elsewhere on the board
REL_SIGN: J6.2; also elsewhere on the board
~STALL: J6.3; also elsewhere on the board

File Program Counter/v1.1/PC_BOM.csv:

"Id";"Designator";"Package";"Quantity";"Designation";"Supplier and ref";
1;"H8,H7,H6,H5";"MountingHole_3.5mm_Pad_Via";4;"MountingHole_Pad";;;
2;"H4,H3,H2,H1";"MountingHole_3.5mm_Pad_Via";4;"MountingHole";;;
3;"C13,C12,C11,C9,C8,C7,C6,C5,C4,C2,C1";"C_Axial_L5.1mm_D3.1mm_P7.50mm_Horizontal";11;"100nF";;;
4;"C10";"C_Axial_L5.1mm_D3.1mm_P7.50mm_Horizontal";1;"100nf";;;
5;"C3";"C_Axial_L5.1mm_D3.1mm_P7.50mm_Horizontal";1;"C?";;;
6;"REG8.2,REG8.1";"DIP-24_W7.62mm";2;"74F825";;;
7;"R14,R10,R5,R4";"R_Axial_DIN0204_L3.6mm_D1.6mm_P7.62mm_Horizontal";4;"10K";;;
8;"R6";"R_Axial_DIN0204_L3.6mm_D1.6mm_P7.62mm_Horizontal";1;"100";;;
9;"POT1";"Potentiometer_Trimmer_ACP_CA14h5_Vertical_Px5.0mm_Py10.0mm";1;"1K";;;
10;"MUXB2,MUXB1,MUXA4,MUXA3,MUXA2,MUXA1";"DIP-16_W7.62mm";6;"74F257";;;
11;"J5";"JST_NV_B02P-NV_2x5.00mm_Vertical";1;"POWER/GND";;;
12;"J4";"1pin";1;"Clock";;;
13;"J3";"JST_XH_B04B-XH-A_04x2.50mm_Straight";1;"Control";;;
14;"J2";"JST_XH_B16B-XH-A_16x2.50mm_Straight";1;"PC_OFFS";;;
15;"J1";"JST_XH_B16B-XH-A_16x2.50mm_Straight";1;"PC_OUT";;;
16;"C_BOARD1";"CP_Radial_D8.0mm_P2.50mm";1;"10uF";;;
17;"ADD4.2,ADD4.1,ADD4.3,ADD4.4";"DIP-16_W7.62mm";4;"74F283";;;

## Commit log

2021-10-21 20oct
    Last progress on evening of October 20
2021-10-23 oct22
2021-10-23 24oct
2021-10-25 25oct
2021-10-27 27oct
    Finished v1.0 of ALU, PC and GP RF.
    Updated documentation to match.
2021-11-02 02nov
    Updated documentation
2021-11-07 08nov
    -Added to documentation
    -Started control signal tables
    -Started v1.1 of PC module
2021-11-11 11nov
    -finished ALU test program on arduino
